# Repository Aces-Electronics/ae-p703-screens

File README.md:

<h1 align="center">

  Ace's Electronics Pty Ltd  
  Touchscreen IO Control for P703 Rangers  
</h1>

# TOC:
1. <a href="#goals">Goals</a>
1. <a href="#current-states">Current States</a>
   - <a href="#reario-screen">RearIO: Screen</a>
   - <a href="#reario-battery">RearIO: Battery</a>
   - <a href="#reario-screen-and-battery-cradle">RearIO: Screen and Battery Cradle</a>
   - <a href="#reario-basic-pcb">RearIO: Basic PCB</a>
   - <a href="#reario-pro-pcb">RearIO: Pro PCB</a>
   - <a href="#frontio-screen">FrontIO: Screen</a>
1. <a href="#android-app">Android App</a>
1. <a href="#where-to-buy">Where to Buy</a>
1. <a href="#support">Support</a>
---
# Goals:
The goal of this project is to simplify the placement and connection of a secondary battery in a P703 Ranger, by:  
- Creating a touchscreen interface for stats and control, one in the cab and one in the tub  
- Minimise what's required to supply secondary battery power to things like fridges/freezers, lights, fans etc.
- Minimise what's required to turn things on and off  
- Display voltages/currents/power/load states and run flat times etc.
- Create a minimilist version that will require some externall hardware like an MPPT dual input controller etc.

# Current States:
## RearIO Screen
Screen has been sourced and basic prototype code has been written. Seems workable for now but more work is needed.

Screen (WT32-SC01 Plus):  

Buy:
https://core-electronics.com.au/wt32-sc01-plus-esp32-development-board-with-35-inch-lcd-ips-display-touch-screen.html

Datasheet:
https://www.marutsu.co.jp/contents/shop/marutsu/datasheet/khe_WT32-SC01-PLUS.pdf

Basic GUI example: 
It's a WIP, but here's a taste:  

## RearIO Battery
50Ah battery has een sourced and tested.  

## RearIO Screen and Battery Cradle
The screen and PCB mount is complete. It has cutouts for a marine grade 12v socket + an Anderson socket, and 2 x Anderson sockets.

## RearIO Basic PCB
basic io screenshot The project is currently in the prototyping phase. The PCBs have been sent to JLCPCB and should be here, along with the components, in the next couple of weeks.  
Files: https://github.com/Aces-Electronics/ae-p703-screens/releases/tag/v0.1

## RearIO Pro PCB
The project is in the design stage, and is coming along as time allows.

## FrontIO Screen
Screen has been sourced. No testing has been done yet.
https://www.makerfabs.com/matouch-esp32-s3-parallel-tft-with-touch-1-9-inch.html  

## Android App
Not yet started

# Where to Buy:
TBA

## Support:
Contact me direct via ace<@>aceselectronics.com.au, just make it look like a normal email address. (hiding from the bots ;) )

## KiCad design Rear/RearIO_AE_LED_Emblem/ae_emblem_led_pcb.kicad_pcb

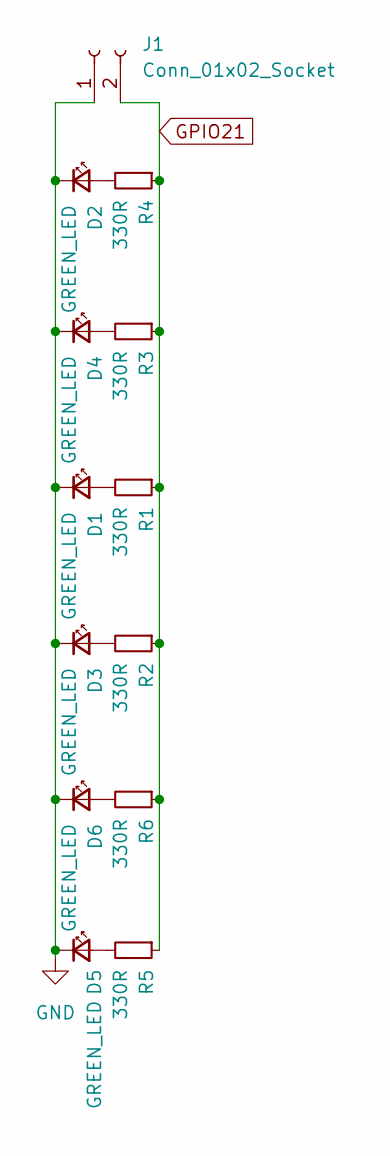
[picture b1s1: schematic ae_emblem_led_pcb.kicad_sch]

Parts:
D1, D2, D3, D4, D5, D6: GREEN_LED; LED_0402_1005Metric; lcsc C434449
J1: Conn_01x02_Socket; Hirose_DF13C_CL535-0402-2-51_1x02-1MP_P1.25mm_Vertical; lcsc C3029359
R1, R2, R3, R4, R5, R6: 330R; R_0402_1005Metric; lcsc C12246

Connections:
GND: D1.1 (K), D2.1 (K), D3.1 (K), D4.1 (K), D5.1 (K), D6.1 (K), J1.1
GPIO21: J1.2, R1.1, R2.1, R3.1, R4.1, R5.1, R6.1
unnamed: D1.2 (A), R1.2
unnamed: D2.2 (A), R4.2
unnamed: D3.2 (A), R2.2
unnamed: D4.2 (A), R3.2
unnamed: D5.2 (A), R5.2
unnamed: D6.2 (A), R6.2

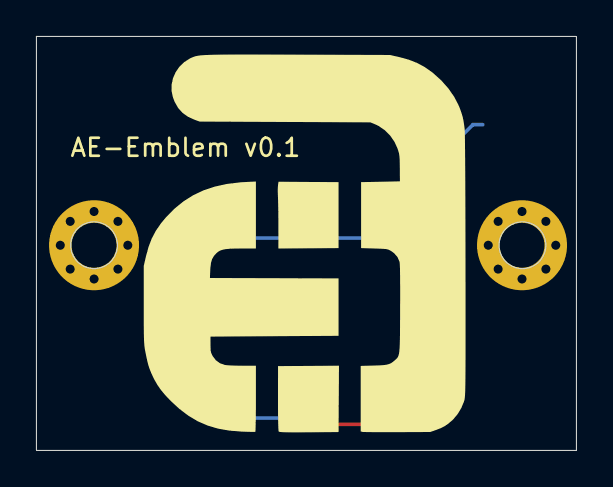
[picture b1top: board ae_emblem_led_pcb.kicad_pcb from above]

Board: 2 copper layers, 30.0 x 23.0 mm, 13 parts (1 on the bottom side), 8 nets.

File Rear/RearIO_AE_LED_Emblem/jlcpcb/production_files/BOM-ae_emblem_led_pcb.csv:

Comment,Designator,Footprint,LCSC
330R,"R1,R2,R3,R4,R5,R6",R_0402_1005Metric,C12246
Conn_01x02_Socket,J1,Hirose_DF13C_CL535-0402-2-51_1x02-1MP_P1.25mm_Vertical,C3029359
GREEN_LED,"D1,D2,D3,D4,D5,D6",LED_0402_1005Metric,C434449

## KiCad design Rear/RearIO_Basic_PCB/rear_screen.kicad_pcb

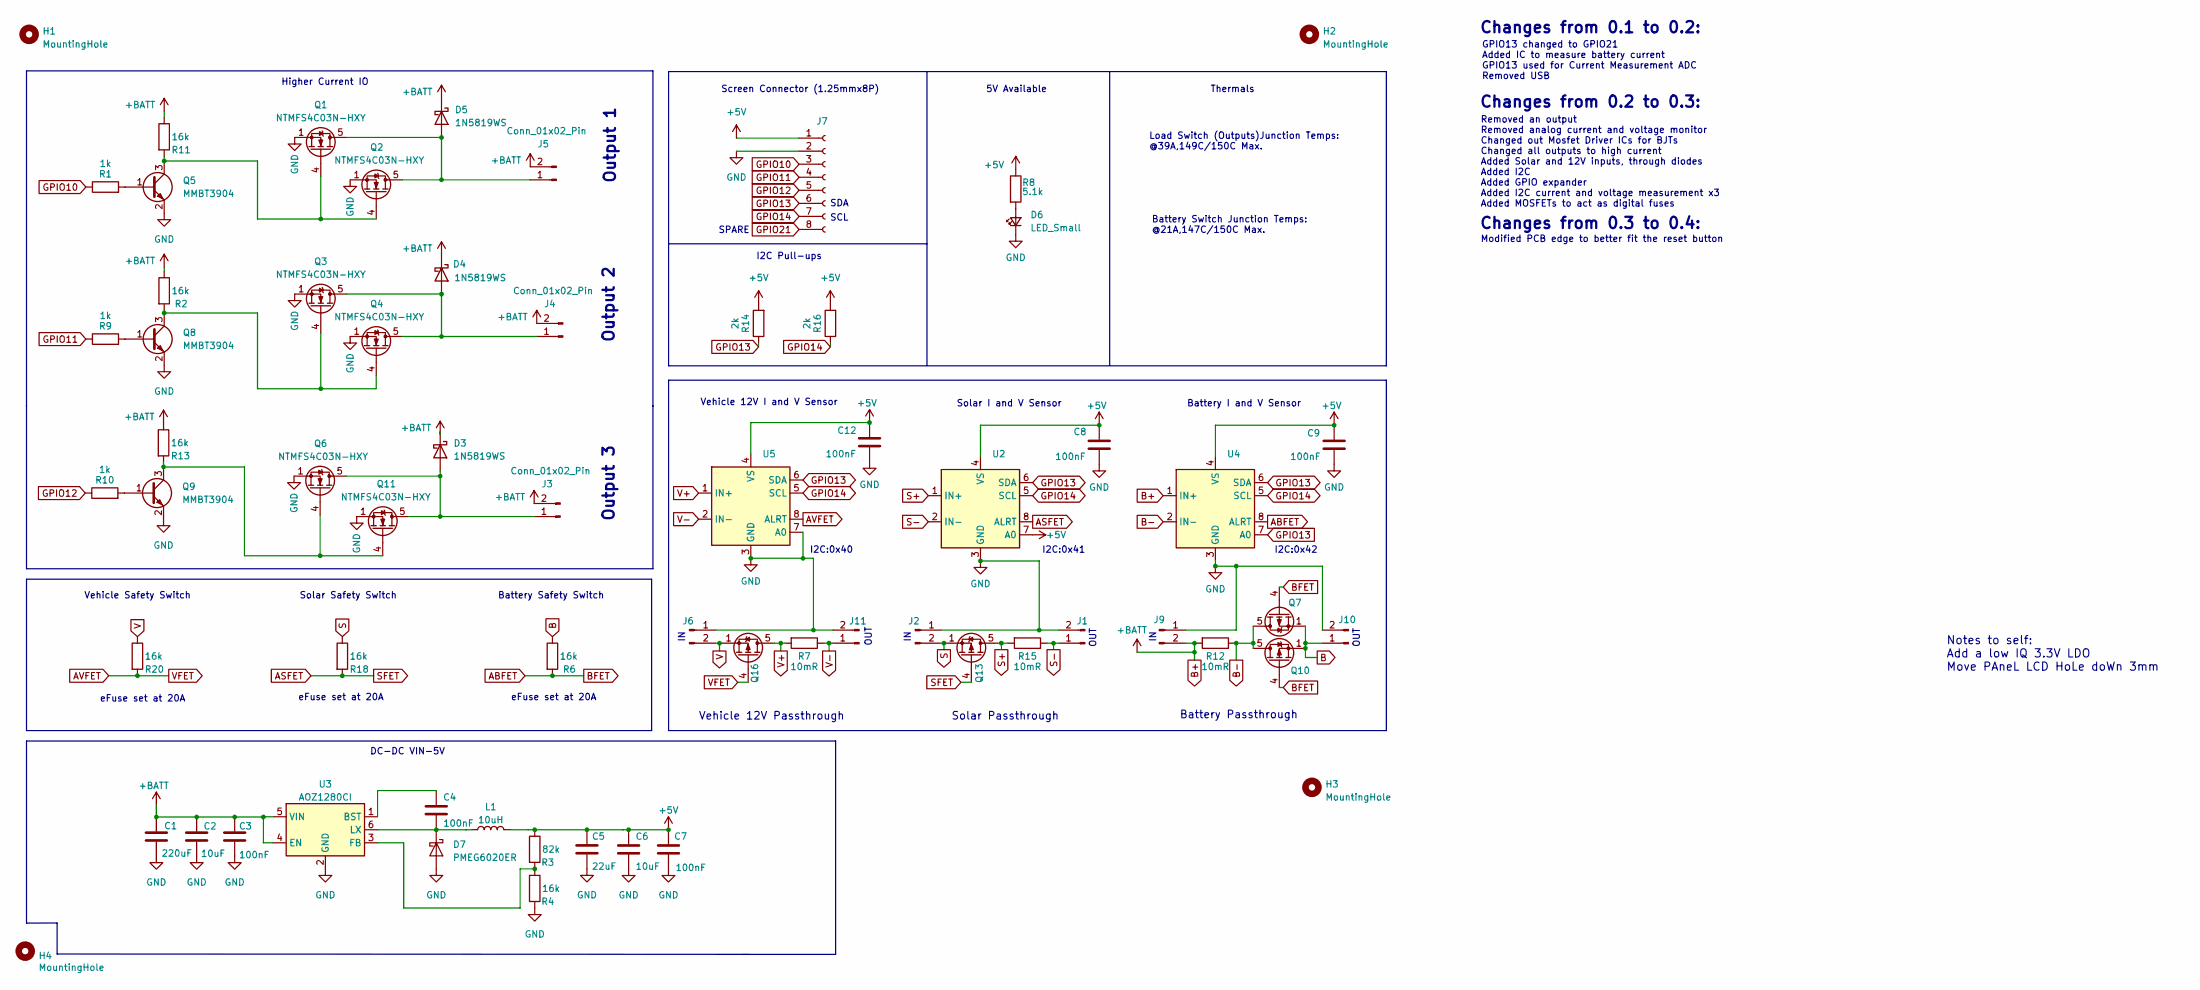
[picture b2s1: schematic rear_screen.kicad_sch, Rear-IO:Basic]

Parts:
C1: 220uF; CP_Elec_6.3x7.7; lcsc C340768
C2, C6: 10uF; C_0603_1608Metric; lcsc C30926
C3, C4, C7, C8, C9, C12: 100nF; C_0603_1608Metric; lcsc C30926
C5: 22uF; CP_Elec_6.3x5.4; lcsc C98744
D3, D4, D5: 1N5819WS; D_SOD-323; lcsc C2927280
D6: LED_Small; LED_0603_1608Metric; lcsc C84264
D7: PMEG6020ER; Nexperia_CFP3_SOD-123W; lcsc C98663
H1, H2, H3, H4: MountingHole; MountingHole_3.2mm_M3_DIN965_Pad
J1, J3, J4, J5, J11: Conn_01x02_Pin; AMASS_XT60PW-F_1x02_P7.20mm_Horizontal; lcsc C428722
J2, J9: Conn_01x02_Pin; AMASS_XT60PW-M_1x02_P7.20mm_Horizontal; lcsc C98732
J6, J10: Conn_01x02_Pin; AMASS_XT90PW-M; lcsc C3040689
J7: Conn_01x08_Socket; BOOMELE-Boom-Precision-Elec-C53040_C53040; lcsc C53040
L1: 10uH; L_Chilisin_BMRA00040415; lcsc C2847473
Q1, Q2, Q3, Q4, Q6, Q11: NTMFS4C03N-HXY; LFPAK56; lcsc C5148663
Q5, Q8, Q9: MMBT3904; SOT-23; lcsc C8512
Q7, Q10, Q13, Q16: AON6411; PowerDI5060-8; lcsc C397981
R1, R9, R10: 1k; R_0603_1608Metric; lcsc C21190
R2, R4, R6, R11, R13, R18, R20: 16k; R_0603_1608Metric; lcsc C4210
R3: 82k; R_0603_1608Metric; lcsc C103831
R7, R12, R15: 10mR; 2728R_C500749; lcsc C500749
R8: 5.1k; R_0603_1608Metric; lcsc C23186
R14, R16: 2k; R_0603_1608Metric; lcsc C22975
U2, U4, U5: INA236AIDDFR_C5443912; SOT-23-8; lcsc C5443912
U3: AOZ1280CI; SOT-23-6; lcsc C5123971

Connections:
+5V: C5.1, C6.1, C7.1, C8.1, C9.1, C12.1, J7.1, L1.2, R3.1, R8.1, R14.2, R16.2, U2.4 (VS), U2.7 (A0), U4.4 (VS), U5.4 (VS)
ABFET: Q7.4 (G), Q10.4 (G), R6.2, U4.8 (ALRT)
ASFET: Q13.4 (G), R18.2, U2.8 (ALRT)
AVFET: Q16.4 (G), R20.2, U5.8 (ALRT)
B: J10.1, Q7.1 (S), Q7.2 (S), Q7.3 (S), Q10.1 (S), Q10.2 (S), Q10.3 (S), R6.1
B+: C1.1, C2.1, C3.1, D3.1 (K), D4.1 (K), D5.1 (K), J3.2, J4.2, J5.2, J9.2, R2.1, R11.1, R12.2, R13.1, U3.4 (EN), U3.5 (VIN), U4.1 (IN+)
B-: Q7.5 (D), Q10.5 (D), R12.1, U4.2 (IN-)
GND: C1.2, C2.2, C3.2, C5.2, C6.2, C7.2, C8.2, C9.2, C12.2, D6.1 (K), D7.2 (A), J1.2, J2.1, J6.1, J7.2, J9.1, J10.2, J11.2, Q1.1 (S), Q1.2 (S), Q1.3 (S), Q2.1 (S), Q2.2 (S), Q2.3 (S), Q3.1 (S), Q3.2 (S), Q3.3 (S), Q4.1 (S), Q4.2 (S), Q4.3 (S), Q5.2 (E), Q6.1 (S), Q6.2 (S), Q6.3 (S), Q8.2 (E), Q9.2 (E), Q11.1 (S), Q11.2 (S), Q11.3 (S), R4.2, U2.3 (GND), U3.2 (GND), U4.3 (GND), U5.3 (GND), U5.7 (A0)
GPIO10: J7.3, R1.1
GPIO11: J7.4, R9.1
GPIO12: J7.5, R10.1
GPIO13: J7.6, R14.1, U2.6 (SDA), U4.6 (SDA), U4.7 (A0), U5.6 (SDA)
GPIO14: J7.7, R16.1, U2.5 (SCL), U4.5 (SCL), U5.5 (SCL)
GPIO21: J7.8
unnamed: D3.2 (A), J3.1, Q6.5 (D), Q11.5 (D)
unnamed: D4.2 (A), J4.1, Q3.5 (D), Q4.5 (D)
unnamed: D5.2 (A), J5.1, Q1.5 (D), Q2.5 (D)
unnamed: D6.2 (A), R8.2
unnamed: C4.2, D7.1 (K), L1.1, U3.6 (LX)
unnamed: Q1.4 (G), Q2.4 (G), Q5.3 (C), R11.2
unnamed: Q3.4 (G), Q4.4 (G), Q8.3 (C), R2.2
unnamed: Q5.1 (B), R1.2
unnamed: Q8.1 (B), R9.2
unnamed: Q9.1 (B), R10.2
unnamed: Q6.4 (G), Q9.3 (C), Q11.4 (G), R13.2
unnamed: C4.1, U3.1 (BST)
unnamed: R3.2, R4.1, U3.3 (FB)
S: J2.2, Q13.1 (S), Q13.2 (S), Q13.3 (S), R18.1
S+: Q13.5 (D), R15.2, U2.1 (IN+)
S-: J1.1, R15.1, U2.2 (IN-)
V: J6.2, Q16.1 (S), Q16.2 (S), Q16.3 (S), R20.1
V+: Q16.5 (D), R7.2, U5.1 (IN+)
V-: J11.1, R7.1, U5.2 (IN-)

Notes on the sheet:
Higher Current IO
I2C:0x40
Changes from 0.3 to 0.4:
Changes from 0.2 to 0.3:
Vehicle Safety Switch
I2C:0x41
Battery Passthrough
Load Switch (Outputs)Junction Temps: @39A,149C/150C Max.
OUT
eFuse set at 20A
Output 2
Battery Switch Junction Temps: @21A,147C/150C Max.
DC-DC VIN-5V
Output 1
Vehicle 12V Passthrough
Screen Connector (1.25mmx8P)
Vehicle 12V I and V Sensor
Output 3
Solar Safety Switch
Changes from 0.1 to 0.2:
I2C:0x42
Battery I and V Sensor
Solar I and V Sensor
Battery Safety Switch
Removed an output Removed analog current and voltage monitor Changed out Mosfet Driver ICs for BJTs Changed all outputs to high current Added Solar and 12V inputs, through diodes Added I2C Added GPIO expander Added I2C current and voltage measurement x3 Added MOSFETs to act as digital fuses
I2C Pull-ups
Modified PCB edge to better fit the reset button
SDA
Thermals
SPARE
5V Available
Notes to self: Add a low IQ 3.3V LDO Move PAneL LCD HoLe doWn 3mm
Solar Passthrough
SCL
GPIO13 changed to GPIO21 Added IC to measure battery current GPIO13 used for Current Measurement ADC Removed USB

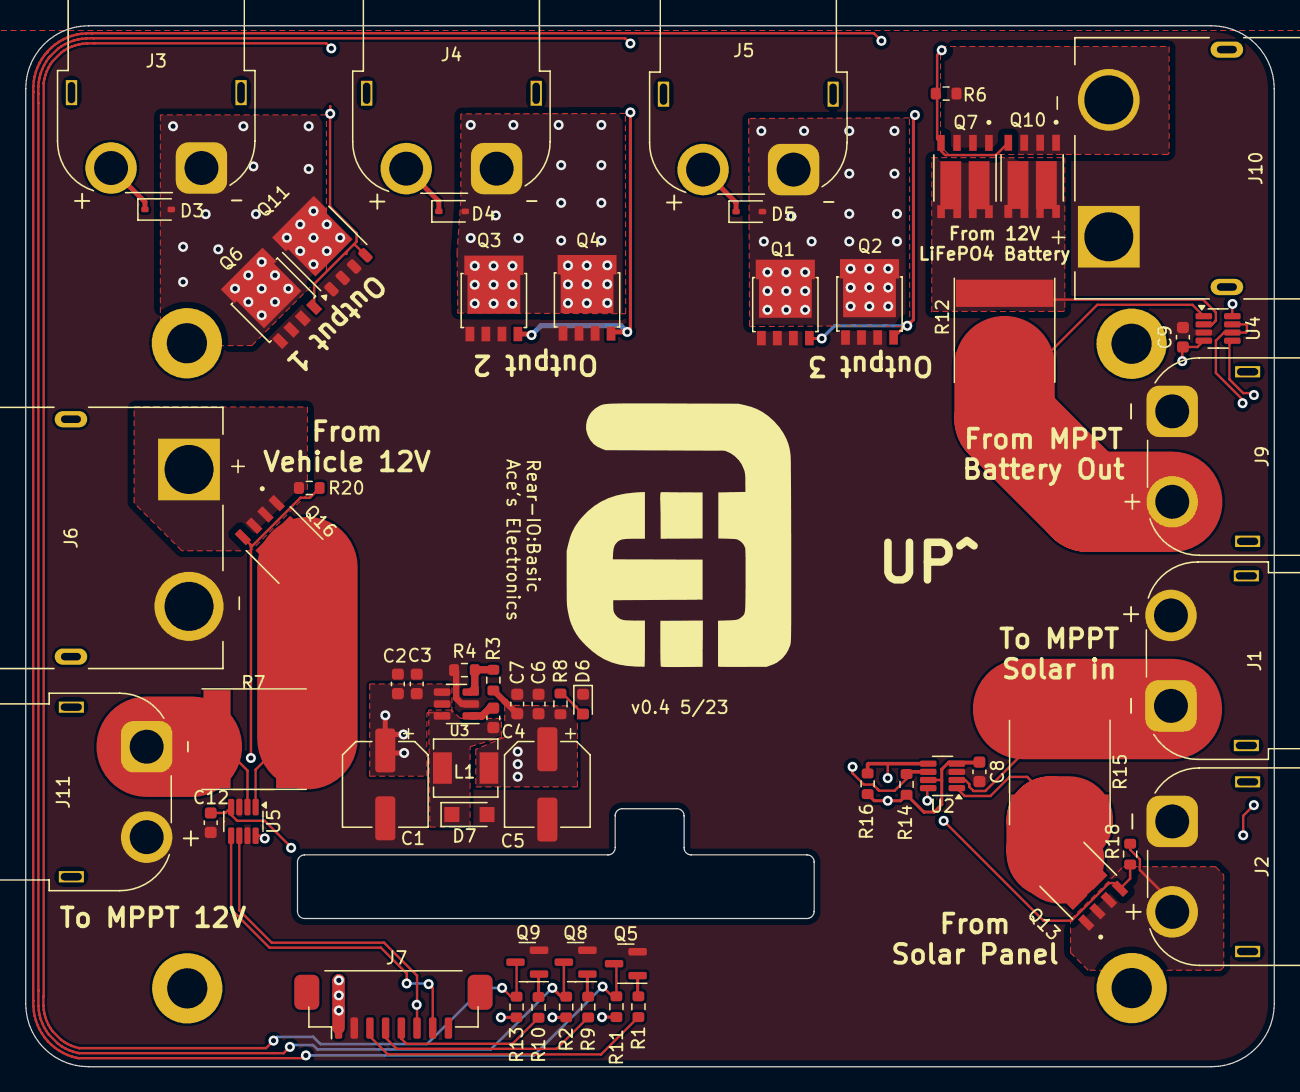
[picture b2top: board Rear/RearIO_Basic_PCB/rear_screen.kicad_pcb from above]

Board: 4 copper layers, 99.4 x 82.9 mm, 64 parts (0 on the bottom side), 32 nets.

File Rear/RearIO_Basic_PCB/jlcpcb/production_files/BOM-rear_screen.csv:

Comment,Designator,Footprint,LCSC
82k,R3,R_0603_1608Metric,C103831
1k,"R1,R10,R9",R_0603_1608Metric,C21190
2k,"R14,R16",R_0603_1608Metric,C22975
5.1k,R8,R_0603_1608Metric,C23186
10uH,L1,L_Chilisin_BMRA00040415,C2847473
1N5819WS,"D3,D4,D5",D_SOD-323,C2927280
Conn_01x02_Pin,"J10,J6",AMASS_XT90PW-M,C3040689
100nF,"C12,C2,C3,C4,C6,C7,C8,C9",C_0603_1608Metric,C30926
220uF,C1,CP_Elec_6.3x7.7,C340768
AON6411,"Q10,Q13,Q16,Q7",PowerDI5060-8,C397981
16k,"R11,R13,R18,R2,R20,R4,R6",R_0603_1608Metric,C4210
Conn_01x02_Pin,"J1,J11,J3,J4,J5",AMASS_XT60PW-F_1x02_P7.20mm_Horizontal,C428722
10mR,"R12,R15,R7",2728R_C500749,C500749
AOZ1280CI,U3,SOT-23-6,C5123971
NTMFS4C03N-HXY,"Q1,Q11,Q2,Q3,Q4,Q6",LFPAK56,C5148663
Conn_01x08_Socket,J7,BOOMELE-Boom-Precision-Elec-C53040_C53040,C53040
INA236AIDDFR_C5443912,"U2,U4,U5",SOT-23-8,C5443912
LED_Small,D6,LED_0603_1608Metric,C84264
MMBT3904,"Q5,Q8,Q9",SOT-23,C8512
PMEG6020ER,D7,Nexperia_CFP3_SOD-123W,C98663
Conn_01x02_Pin,"J2,J9",AMASS_XT60PW-M_1x02_P7.20mm_Horizontal,C98732
22uF,C5,CP_Elec_6.3x5.4,C98744

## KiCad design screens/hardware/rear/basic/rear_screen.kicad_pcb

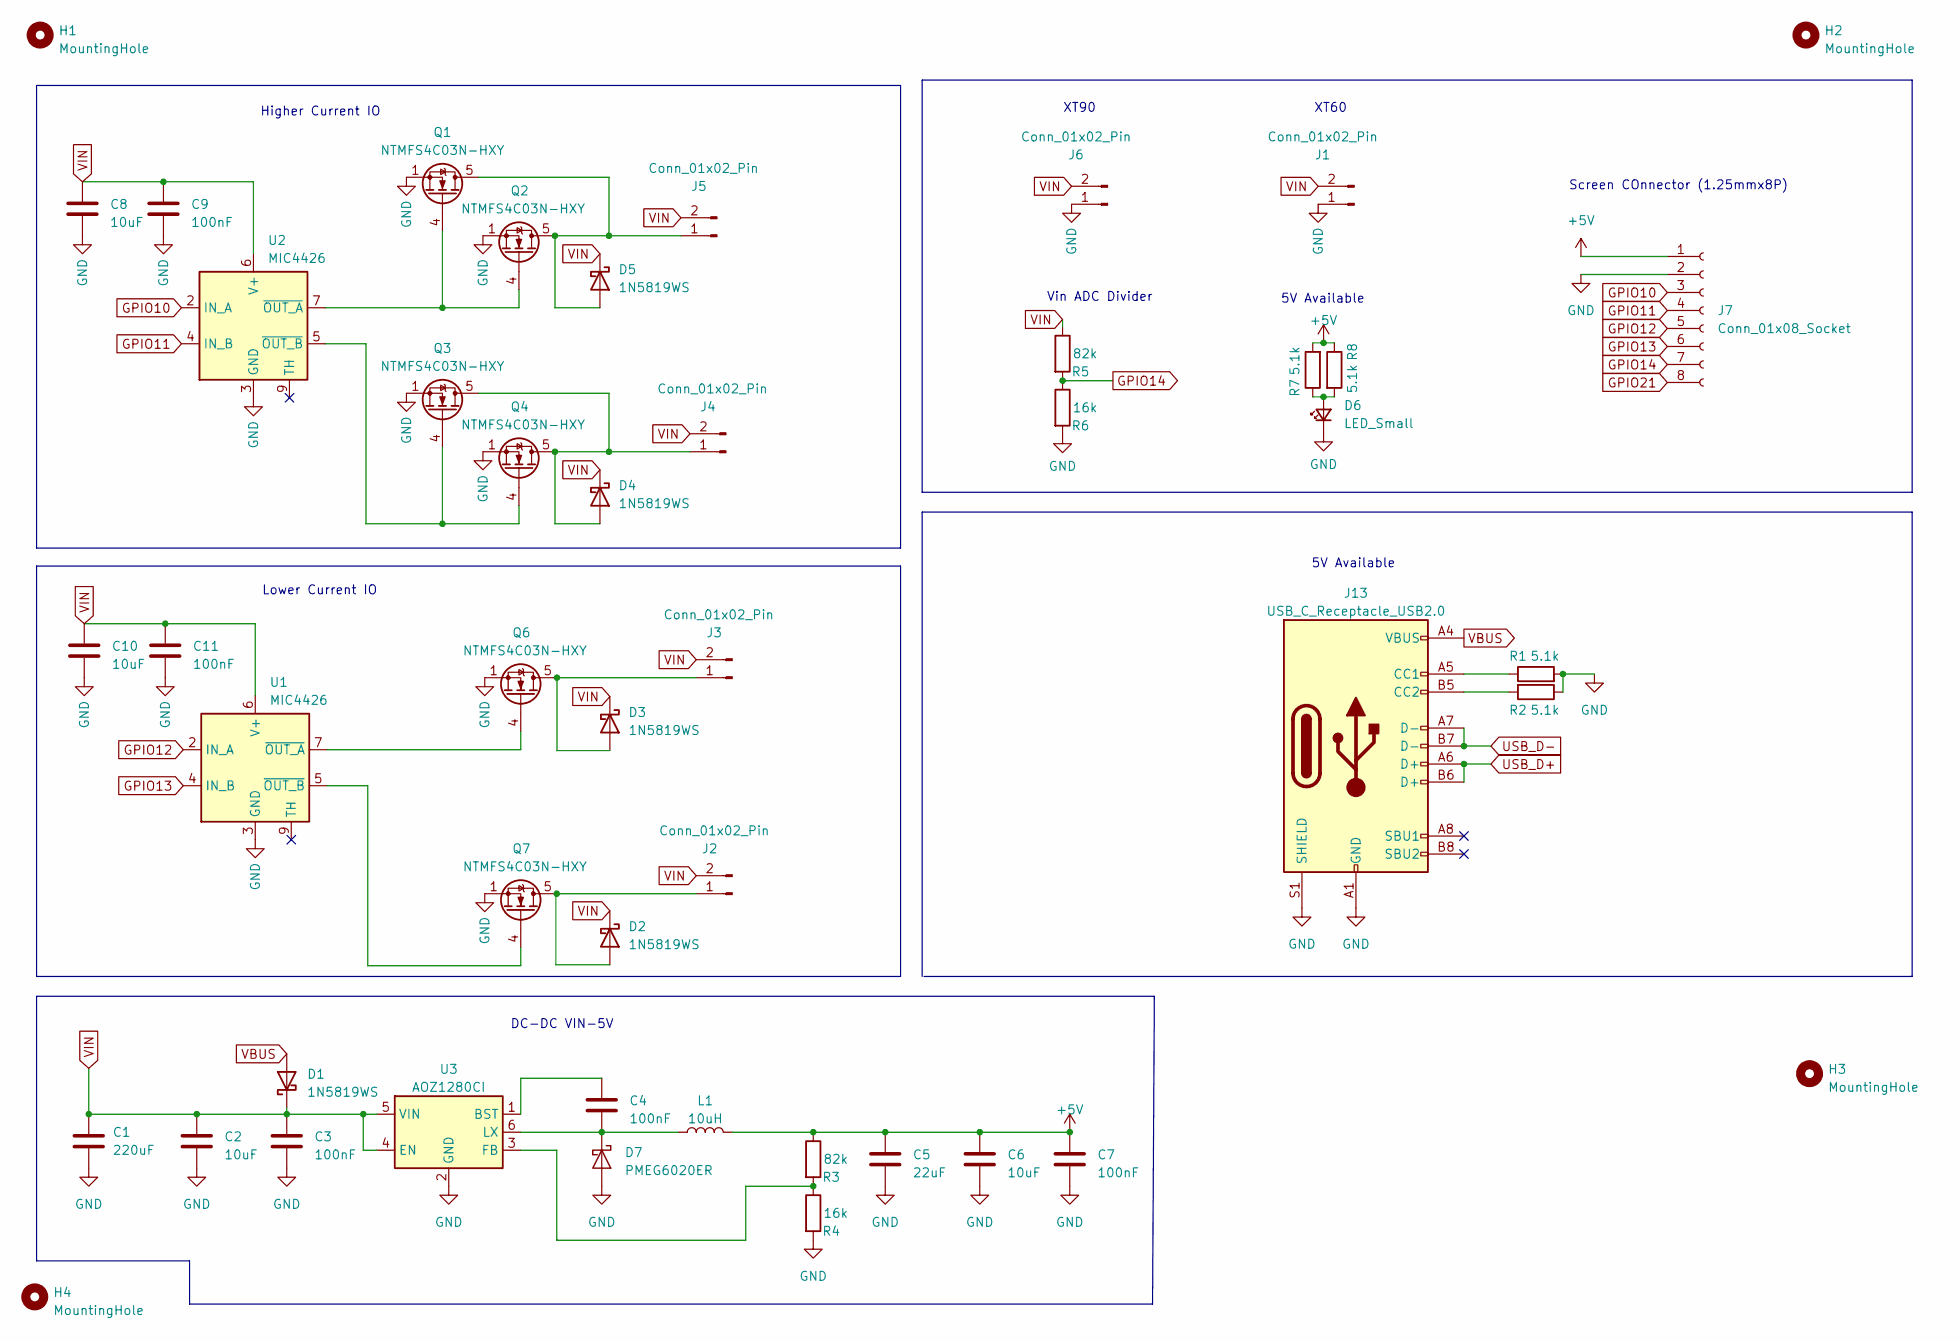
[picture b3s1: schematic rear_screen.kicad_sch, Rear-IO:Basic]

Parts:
C1: 220uF; CP_Elec_6.3x7.7; lcsc C99836
C2, C6, C8, C10: 10uF; C_0603_1608Metric; lcsc C30926
C3, C4, C7, C9, C11: 100nF; C_0603_1608Metric; lcsc C30926
C5: 22uF; CP_Elec_6.3x5.4; lcsc C98744
D1, D2, D3, D4, D5: 1N5819WS; D_SOD-323; lcsc C2927280
D6: LED_Small; LED_0603_1608Metric; lcsc C84264
D7: PMEG6020ER; Nexperia_CFP3_SOD-123W; lcsc C98663
H1, H2, H3, H4: MountingHole; MountingHole_3.2mm_M3_DIN965_Pad
J1: Conn_01x02_Pin; AMASS_XT60PW-M_1x02_P7.20mm_Horizontal; lcsc C98732
J2, J3, J4, J5: Conn_01x02_Pin; AMASS_XT60PW-F_1x02_P7.20mm_Horizontal; lcsc C428722
J6: Conn_01x02_Pin; AMASS_XT90PW-M; lcsc C3040689
J7: Conn_01x08_Socket; BOOMELE-Boom-Precision-Elec-C53040_C53040; lcsc C53040
J13: USB_C_Receptacle_USB2.0; USB_C_Receptacle_G-Switch_GT-USB-7010ASV; lcsc C2988369
L1: 10uH; L_Chilisin_BMRA00040415; lcsc C2847473
Q1, Q2, Q3, Q4, Q6, Q7: NTMFS4C03N-HXY; LFPAK56; lcsc C5148663
R1, R2, R7, R8: 5.1k; R_0603_1608Metric; lcsc C23186
R3, R5: 82k; R_0603_1608Metric; lcsc C103831
R4, R6: 16k; R_0603_1608Metric; lcsc C4210
U1, U2: MIC4426; HSOP-8-1EP_3.9x4.9mm_P1.27mm_EP2.41x3.1mm_ThermalVias; lcsc C2685358
U3: AOZ1280CI; SOT-23-6; lcsc C5123971

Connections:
+5V: C5.1, C6.1, C7.1, J7.1, L1.2, R3.1, R7.2, R8.1
GND: C1.2, C2.2, C3.2, C5.2, C6.2, C7.2, C8.2, C9.2, C10.2, C11.2, D6.1 (K), D7.2 (A), J1.1, J6.1, J7.2, J13.A1 (GND), J13.A12 (GND), J13.B1 (GND), J13.B12 (GND), J13.S1 (SHIELD), Q1.1 (S), Q1.2 (S), Q1.3 (S), Q2.1 (S), Q2.2 (S), Q2.3 (S), Q3.1 (S), Q3.2 (S), Q3.3 (S), Q4.1 (S), Q4.2 (S), Q4.3 (S), Q6.1 (S), Q6.2 (S), Q6.3 (S), Q7.1 (S), Q7.2 (S), Q7.3 (S), R1.2, R2.1, R4.2, R6.2, U1.3 (GND), U2.3 (GND), U3.2 (GND)
GPIO10: J7.3, U2.2 (IN_A)
GPIO11: J7.4, U2.4 (IN_B)
GPIO12: J7.5, U1.2 (IN_A)
GPIO13: J7.6, U1.4 (IN_B)
GPIO14: J7.7, R5.2, R6.1
GPIO21: J7.8
unnamed: D2.2 (A), J2.1, Q7.5 (D)
unnamed: D3.2 (A), J3.1, Q6.5 (D)
unnamed: D4.2 (A), J4.1, Q3.5 (D), Q4.5 (D)
unnamed: D5.2 (A), J5.1, Q1.5 (D), Q2.5 (D)
unnamed: D6.2 (A), R7.1, R8.2
unnamed: C4.2, D7.1 (K), L1.1, U3.6 (LX)
unnamed: J13.A5 (CC1), R1.1
unnamed: J13.B5 (CC2), R2.2
unnamed: Q1.4 (G), Q2.4 (G), U2.7 (~OUT_A)
unnamed: Q3.4 (G), Q4.4 (G), U2.5 (~OUT_B)
unnamed: Q6.4 (G), U1.7 (~OUT_A)
unnamed: Q7.4 (G), U1.5 (~OUT_B)
unnamed: C4.1, U3.1 (BST)
unnamed: R3.2, R4.1, U3.3 (FB)
USB_D+: J13.A6 (D+), J13.B6 (D+)
USB_D-: J13.A7 (D-), J13.B7 (D-)
VBUS: D1.2 (A), J13.A4 (VBUS), J13.A9 (VBUS), J13.B4 (VBUS), J13.B9 (VBUS)
VIN: C1.1, C2.1, C3.1, C8.1, C9.1, C10.1, C11.1, D1.1 (K), D2.1 (K), D3.1 (K), D4.1 (K), D5.1 (K), J1.2, J2.2, J3.2, J4.2, J5.2, J6.2, R5.1, U1.6 (V+), U2.6 (V+), U3.4 (EN), U3.5 (VIN)

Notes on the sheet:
Higher Current IO
Lower Current IO
DC-DC VIN-5V
XT90
Screen COnnector (1.25mmx8P)
5V Available
Vin ADC Divider
XT60

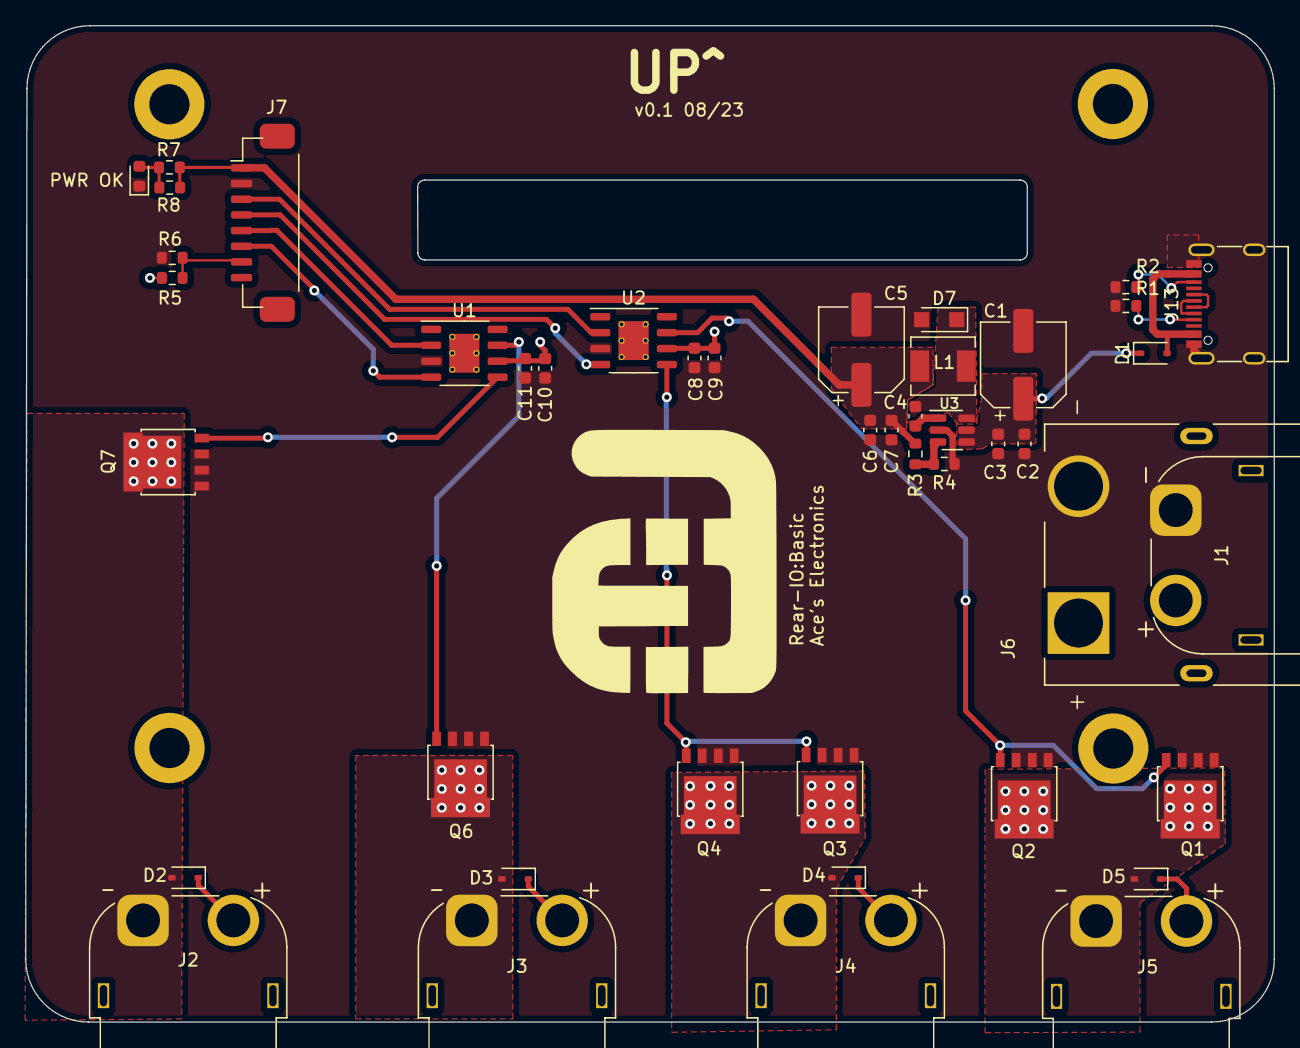
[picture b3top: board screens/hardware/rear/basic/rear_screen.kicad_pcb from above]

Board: 2 copper layers, 99.5 x 79.4 mm, 48 parts (0 on the bottom side), 25 nets.

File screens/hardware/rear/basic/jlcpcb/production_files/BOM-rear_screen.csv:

Comment,Designator,Footprint,LCSC
82k,"R3,R5",R_0603_1608Metric,C103831
5.1k,"R1,R2",R_0603_1608Metric,C23186
MIC4426,"U1,U2",HSOP-8-1EP_3.9x4.9mm_P1.27mm_EP2.41x3.1mm_ThermalVias,C2685358
10uH,L1,L_Chilisin_BMRA00040415,C2847473
1N5819WS,"D1,D2,D3,D4,D5",D_SOD-323,C2927280
USB_C_Receptacle_USB2.0,J13,USB_C_Receptacle_G-Switch_GT-USB-7010ASV,C2988369
Conn_01x02_Pin,J6,AMASS_XT90PW-M,C3040689
10uF,"C10,C11,C2,C3,C4,C6,C7,C8,C9",C_0603_1608Metric,C30926
16k,"R4,R6",R_0603_1608Metric,C4210
Conn_01x02_Pin,"J2,J3,J4,J5",AMASS_XT60PW-F_1x02_P7.20mm_Horizontal,C428722
AOZ1280CI,U3,SOT-23-6,C5123971
NTMFS4C03N-HXY,"Q1,Q2,Q3,Q4,Q6,Q7",LFPAK56,C5148663
Conn_01x08_Socket,J7,BOOMELE-Boom-Precision-Elec-C53040_C53040,C53040
PMEG6020ER,D7,Nexperia_CFP3_SOD-123W,C98663
Conn_01x02_Pin,J1,AMASS_XT60PW-M_1x02_P7.20mm_Horizontal,C98732
22uF,C5,CP_Elec_6.3x5.4,C98744
220uF,C1,CP_Elec_6.3x7.7,C99836

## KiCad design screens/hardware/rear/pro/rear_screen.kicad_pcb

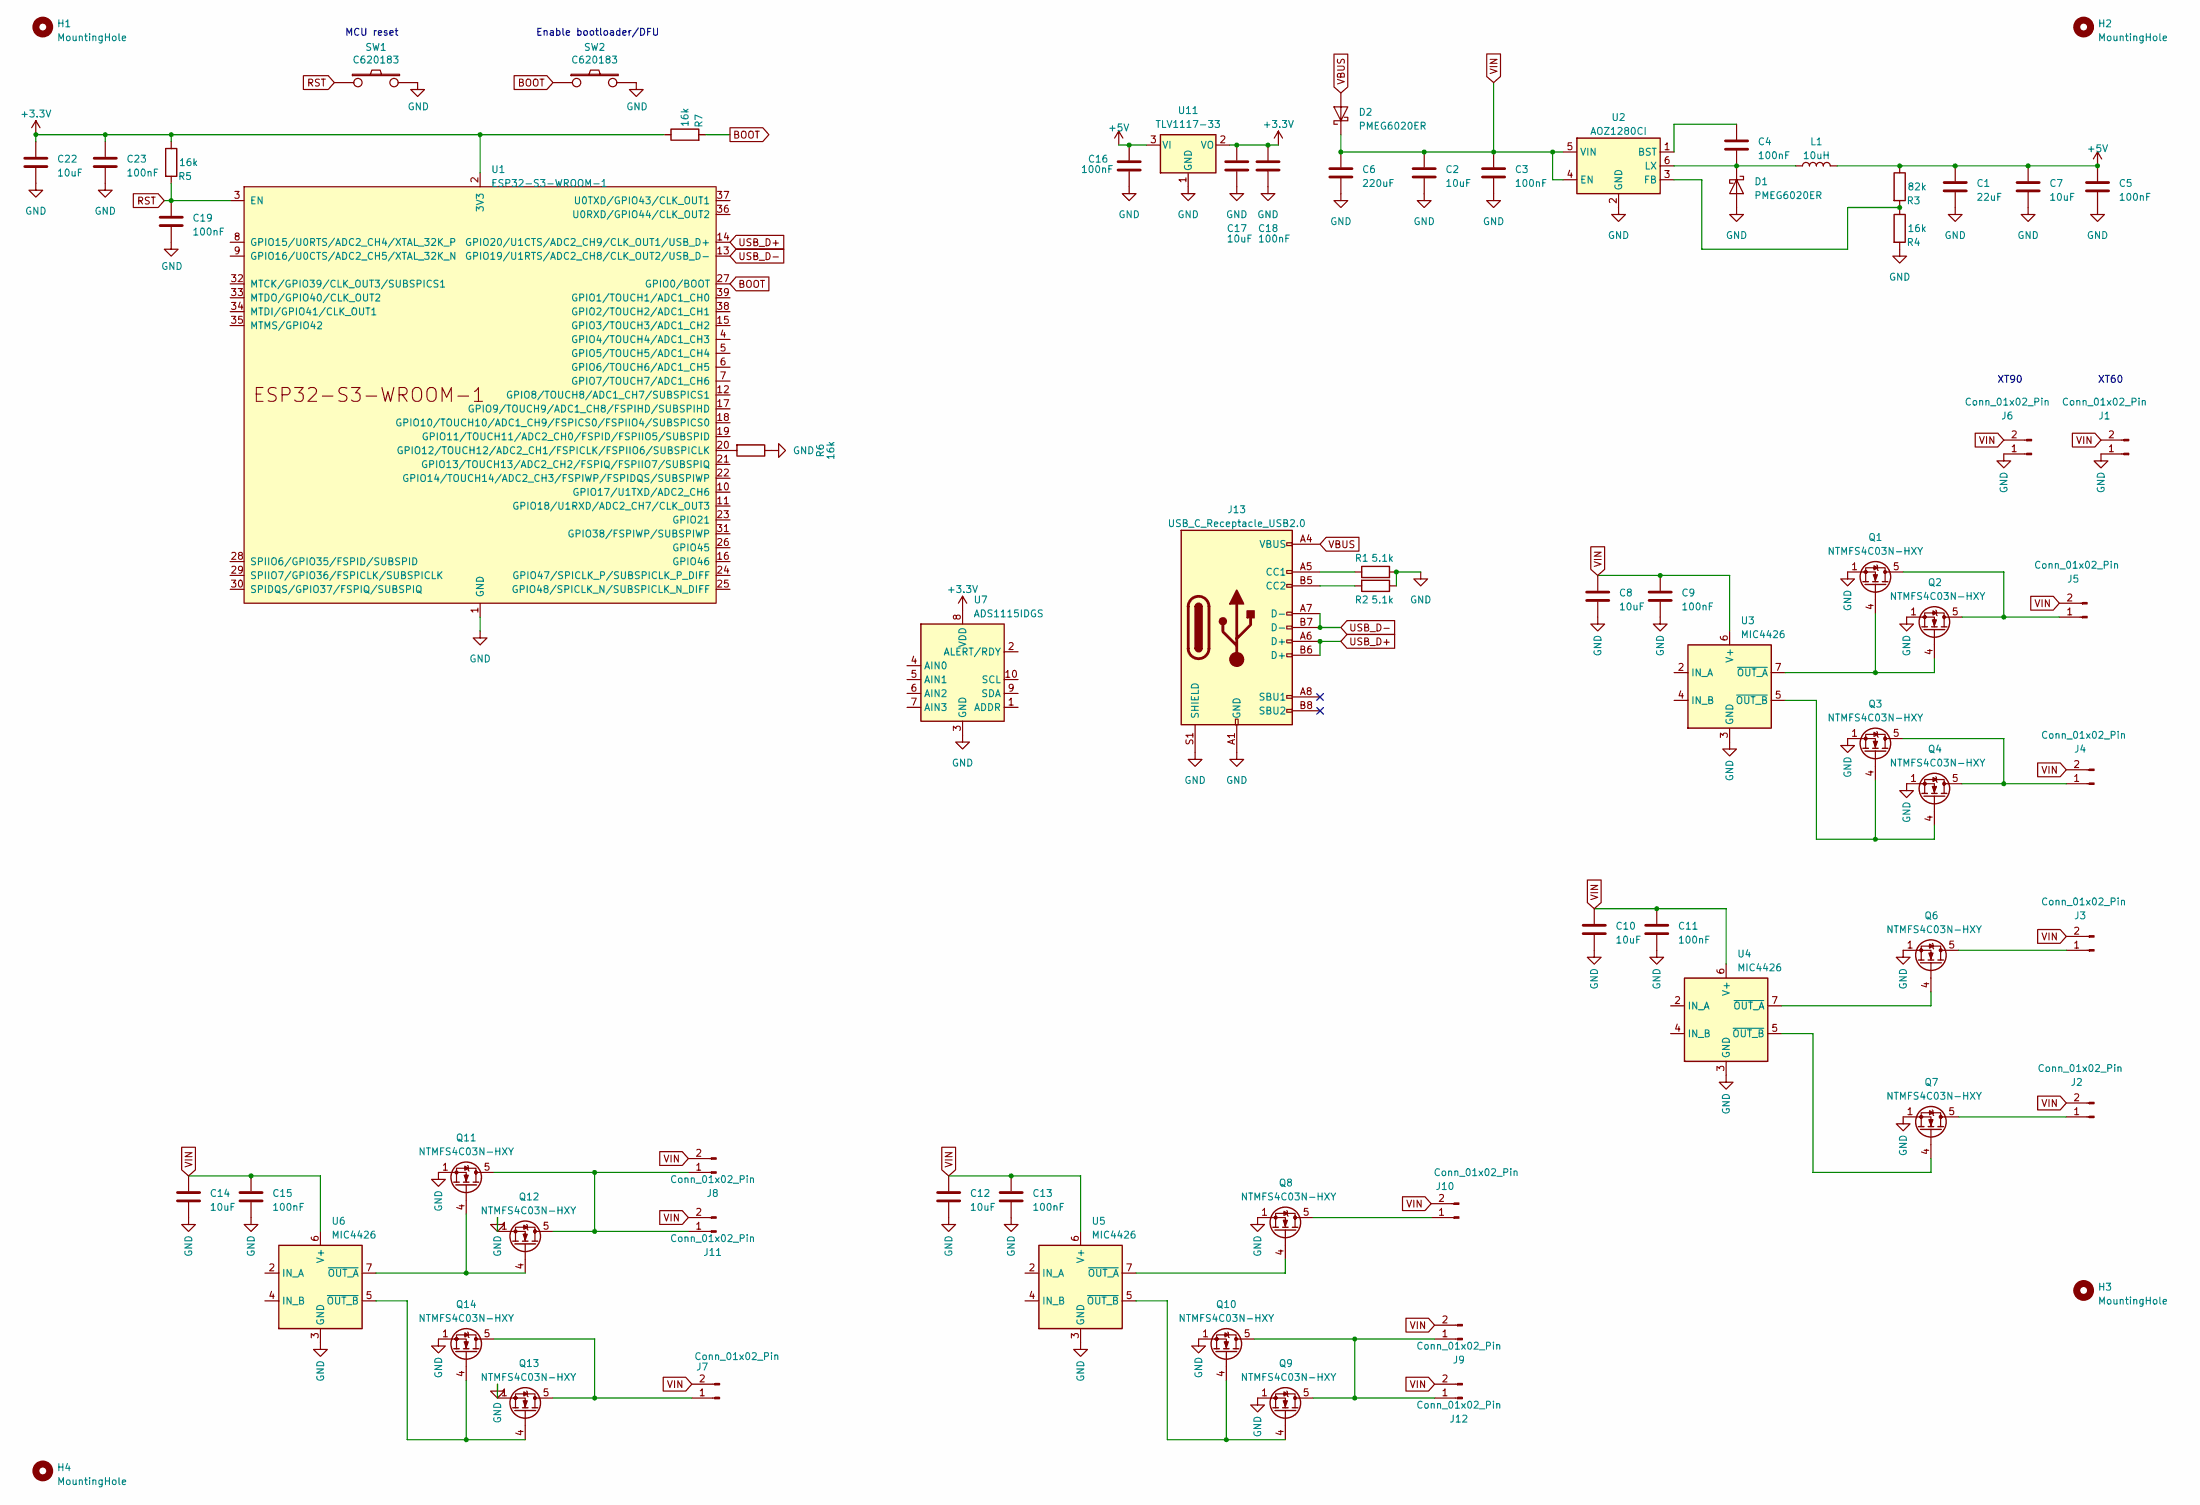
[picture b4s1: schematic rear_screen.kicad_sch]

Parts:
C1: 22uF; CP_Elec_6.3x5.4; lcsc C98744
C2, C7, C8, C10, C12, C14, C17, C22: 10uF; C_0603_1608Metric; lcsc C30926
C3, C4, C5, C9, C11, C13, C15, C16, C18, C19, C23: 100nF; C_0603_1608Metric; lcsc C30926
C6: 220uF; CP_Elec_6.3x7.7; lcsc C99836
D1, D2: PMEG6020ER; Nexperia_CFP3_SOD-123W; lcsc C98663
H1, H2, H3, H4: MountingHole; MountingHole_3.2mm_M3_DIN965_Pad
J1: Conn_01x02_Pin; AMASS_XT60PW-M_1x02_P7.20mm_Horizontal; lcsc C98732
J2, J3, J4, J5, J7, J8, J9, J10: Conn_01x02_Pin; AMASS_XT60PW-F_1x02_P7.20mm_Horizontal; lcsc C428722
J6: Conn_01x02_Pin; AMASS_XT90PW-M; lcsc C3040689
J11, J12: Conn_01x02_Pin; AMASS_XT90PW-F; lcsc C3040690
J13: USB_C_Receptacle_USB2.0; USB_C_Receptacle_G-Switch_GT-USB-7010ASV; lcsc C2988369
L1: 10uH; L_Chilisin_BMRA00040415; lcsc C2847473
Q1, Q2, Q3, Q4, Q6, Q7, Q8, Q9, Q10, Q11, Q12, Q13, Q14: NTMFS4C03N-HXY; LFPAK56; lcsc C5148663
R1, R2: 5.1k; R_0603_1608Metric; lcsc C23186
R3: 82k; R_0603_1608Metric; lcsc C103831
R4, R5, R6, R7: 16k; R_0603_1608Metric; lcsc C4210
SW1: C620183; TS4550TP; lcsc C620183
SW2: C620183; TS4550TP; lcsc_part_number C620183
U1: ESP32-S3-WROOM-1
U2: AOZ1280CI; SOT-23-6; lcsc C5123971
U3, U4, U5, U6: MIC4426; HSOP-8-1EP_3.9x4.9mm_P1.27mm_EP2.41x3.1mm_ThermalVias; lcsc C2685358
U7: ADS1115IDGS; TSSOP-10_3x3mm_P0.5mm
U11: TLV1117-33; SOT-223; lcsc C15578

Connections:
+3.3V: C17.1, C18.1, C22.1, C23.1, R5.1, R7.1, U1.2 (3V3), U7.8 (VDD), U11.2 (VO)
+5V: C1.1, C5.1, C7.1, C16.1, L1.2, R3.1, U11.3 (VI)
BOOT: R7.2, SW2.1, U1.27 (GPIO0/BOOT)
GND: C1.2, C2.2, C3.2, C5.2, C6.2, C7.2, C8.2, C9.2, C10.2, C11.2, C12.2, C13.2, C14.2, C15.2, C16.2, C17.2, C18.2, C19.2, C22.2, C23.2, D1.2 (A), J1.1, J6.1, J13.A1 (GND), J13.A12 (GND), J13.B1 (GND), J13.B12 (GND), J13.S1 (SHIELD), Q1.1 (S), Q1.2 (S), Q1.3 (S), Q2.1 (S), Q2.2 (S), Q2.3 (S), Q3.1 (S), Q3.2 (S), Q3.3 (S), Q4.1 (S), Q4.2 (S), Q4.3 (S), Q6.1 (S), Q6.2 (S), Q6.3 (S), Q7.1 (S), Q7.2 (S), Q7.3 (S), Q8.1 (S), Q8.2 (S), Q8.3 (S), Q9.1 (S), Q9.2 (S), Q9.3 (S), Q10.1 (S), Q10.2 (S), Q10.3 (S), Q11.1 (S), Q11.2 (S), Q11.3 (S), Q12.1 (S), Q12.2 (S), Q12.3 (S), Q13.1 (S), Q13.2 (S), Q13.3 (S), Q14.1 (S), Q14.2 (S), Q14.3 (S), R1.2, R2.1, R4.2, R6.1, SW1.2, SW2.2, U1.1 (GND), U1.40 (GND), U1.41 (GND), U2.2 (GND), U3.3 (GND), U4.3 (GND), U5.3 (GND), U6.3 (GND), U7.3 (GND), U11.1 (GND)
unnamed: C4.2, D1.1 (K), L1.1, U2.6 (LX)
unnamed: J2.1, Q7.5 (D)
unnamed: J3.1, Q6.5 (D)
unnamed: J4.1, Q3.5 (D), Q4.5 (D)
unnamed: J5.1, Q1.5 (D), Q2.5 (D)
unnamed: J7.1, Q13.5 (D), Q14.5 (D)
unnamed: J10.1, Q8.5 (D)
unnamed: J8.1, J11.1, Q11.5 (D), Q12.5 (D)
unnamed: J9.1, J12.1, Q9.5 (D), Q10.5 (D)
unnamed: J13.A5 (CC1), R1.1
unnamed: J13.B5 (CC2), R2.2
unnamed: Q1.4 (G), Q2.4 (G), U3.7 (~OUT_A)
unnamed: Q3.4 (G), Q4.4 (G), U3.5 (~OUT_B)
unnamed: Q6.4 (G), U4.7 (~OUT_A)
unnamed: Q7.4 (G), U4.5 (~OUT_B)
unnamed: Q8.4 (G), U5.7 (~OUT_A)
unnamed: Q9.4 (G), Q10.4 (G), U5.5 (~OUT_B)
unnamed: Q11.4 (G), Q12.4 (G), U6.7 (~OUT_A)
unnamed: Q13.4 (G), Q14.4 (G), U6.5 (~OUT_B)
unnamed: R6.2, U1.20 (GPIO12/TOUCH12/ADC2_CH1/FSPICLK/FSPIIO6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)
unnamed: C4.1, U2.1 (BST)
unnamed: R3.2, R4.1, U2.3 (FB)
RST: C19.1, R5.2, SW1.1, U1.3 (EN)
USB_D+: J13.A6 (D+), J13.B6 (D+), U1.14 (GPIO20/U1CTS/ADC2_CH9/CLK_OUT1/USB_D+)
USB_D-: J13.A7 (D-), J13.B7 (D-), U1.13 (GPIO19/U1RTS/ADC2_CH8/CLK_OUT2/USB_D-)
VBUS: D2.2 (A), J13.A4 (VBUS), J13.A9 (VBUS), J13.B4 (VBUS), J13.B9 (VBUS)
VIN: C2.1, C3.1, C6.1, C8.1, C9.1, C10.1, C11.1, C12.1, C13.1, C14.1, C15.1, D2.1 (K), J1.2, J2.2, J3.2, J4.2, J5.2, J6.2, J7.2, J8.2, J9.2, J10.2, J11.2, J12.2, U2.4 (EN), U2.5 (VIN), U3.6 (V+), U4.6 (V+), U5.6 (V+), U6.6 (V+)

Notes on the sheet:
Enable bootloader/DFU
XT90
MCU reset
XT60

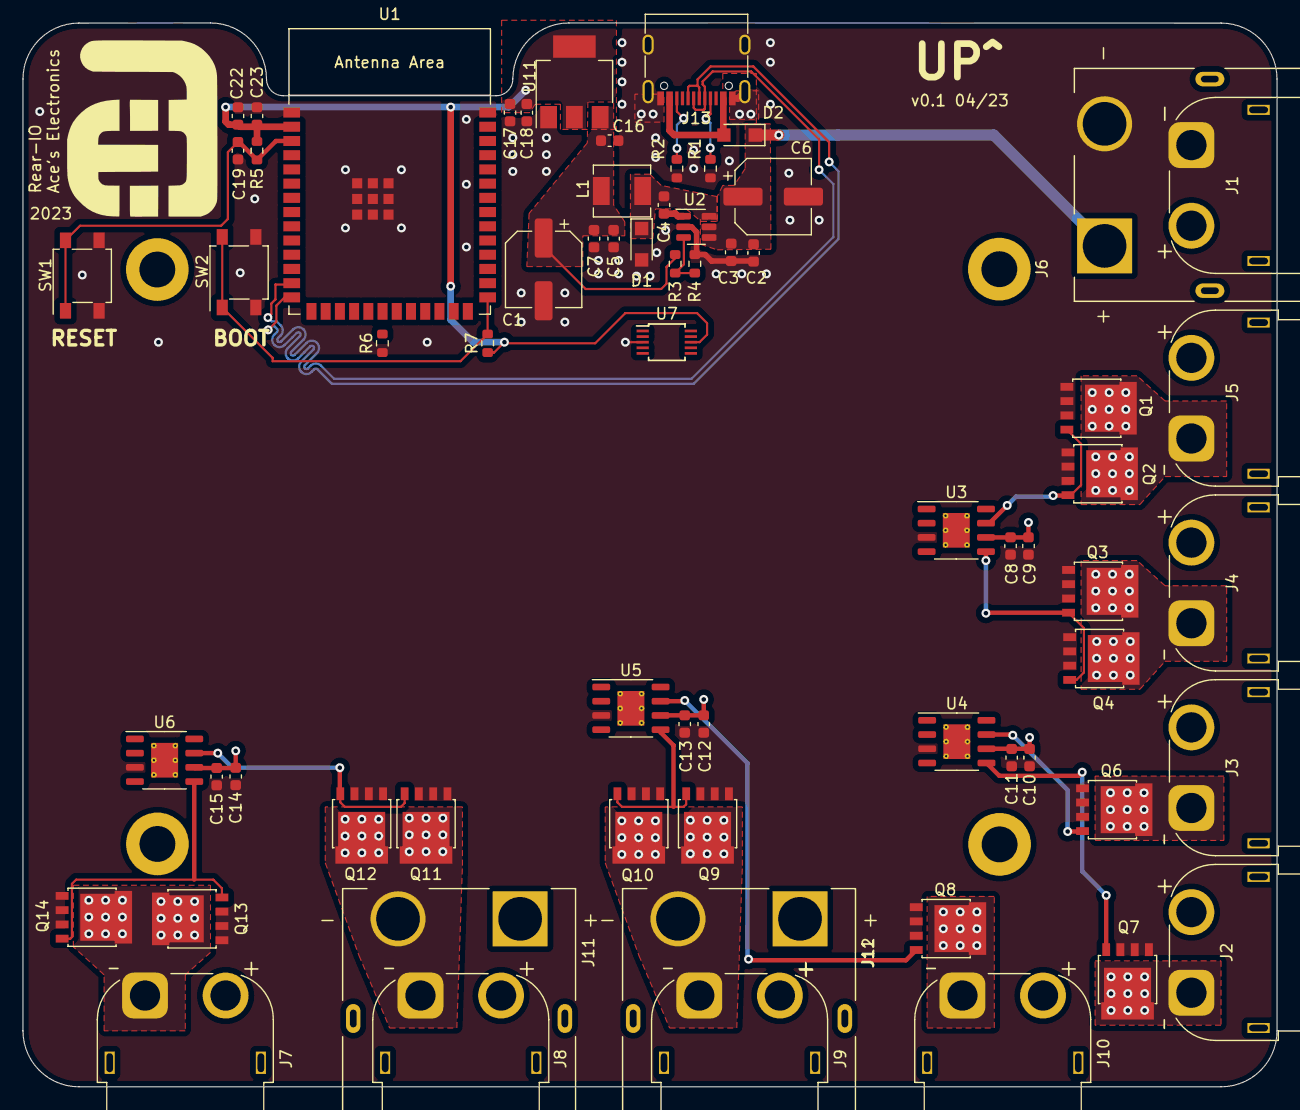
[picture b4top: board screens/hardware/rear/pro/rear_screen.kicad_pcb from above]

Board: 4 copper layers, 112.0 x 95.0 mm, 71 parts (0 on the bottom side), 31 nets.

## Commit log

2023-04-16 First push
2023-04-16 added splash, brightness working
2023-08-19 update, basic board complete
2023-08-19 Sent to JLCPCB as Rev0
2023-08-20 changing layout and updating ReadME
2023-08-20 Added basic connection diagram
2023-08-20 typo
2023-08-20 added screen mount
2023-08-21 Added cradle renders
2023-09-03 ibom
2023-09-05 text input nearly working
2023-09-05 labels saving from input
2023-09-05 All working!!!
2023-09-05 working
2023-09-06 moved text
2023-09-06 added factory reset
2023-09-06 renamed a screen
2023-09-06 don't save null input
2023-09-06 Dynamic battery state updates
2023-09-06 missed a bit
2023-09-06 moved some ui elements around
2023-09-06 small ui changes
2023-09-07 small routing and layout changes, removed USB
2023-09-07 voltage state changes
2023-09-07 routing and layout changes
2023-09-07 removing logging
2023-09-08 v0.2 submitted to JLCPCB
2023-09-08 code polish
2023-09-08 ui polish
2023-09-08 more ui polish
2023-09-11 adding first working front screen code
2023-09-12 before ble
2023-09-12 bidirectional data working
2023-09-14 message rate limiting working
2023-09-14 sync messages working
2023-09-14 standardising code
2023-09-14 and again
2023-09-14 and my axe
2023-09-14 working again after refactor
2023-09-14 massive refactor
2023-09-15 updated lvgl
2023-09-15 buffer overflow fixed!
2023-09-15 one way comms stable
2023-09-15 ui changes
2024-05-28 Started work on v0.3 software
2024-05-28 Partially added INA236
2024-05-28 logic inversion fixed
2024-05-28 Modified UI, removed lp2
2024-05-28 swipe fixed
2024-05-29 UI fixes
2024-05-30 UI is working!!!
2024-05-30 UI finally fixed
2024-05-31 Final UI changes
2025-07-21 save point before modifying front UI
2025-07-21 done, all working
